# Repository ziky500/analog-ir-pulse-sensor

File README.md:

# Analog IR Pulse Sensor

A simple analog infrared pulse sensor based on reflective photoplethysmography (PPG).

The circuit uses an infrared LED and a photodiode to detect small changes in reflected light caused by blood volume changes in a fingertip. The signal is amplified and filtered using an LM358 operational amplifier.

## My work

The original circuit design was provided by the university as a reference.

I:

- recreated the circuit schematic in KiCad based on the provided design,
- designed the PCB layout in KiCad,
- prepared the single-sided board for CNC milling,
- milled and drilled the PCB at the university,
- manually assembled and soldered the board,
- brought the circuit into operation,
- tested the finished sensor.

## PCB design

The PCB was designed as a single-sided through-hole board suitable for CNC milling.

One crossing connection was implemented as a wire jumper.

A complete PCB layout export is available here:

[PCB layout PDF](exports/pcb_layout.pdf)

## Schematic

The original circuit design was provided by the university. I recreated the schematic in KiCad and used it as the basis for the PCB design.

A PDF version is available here:

[Schematic PDF](exports/schematic.pdf)

## Additional PCB exports

- [Bottom copper layer](exports/pcb_bottom_copper.pdf)
- [Top copper layer](exports/pcb_top_copper.pdf)

## Source files

The editable KiCad project files are available in the [`hardware`](hardware/) directory:

- `senzor_tepu.kicad_pro`
- `senzor_tepu.kicad_sch`
- `senzor_tepu.kicad_pcb`

## Acknowledgements

The original circuit design was provided by the Faculty of Electrical Engineering,
Czech Technical University in Prague (CTU FEL).

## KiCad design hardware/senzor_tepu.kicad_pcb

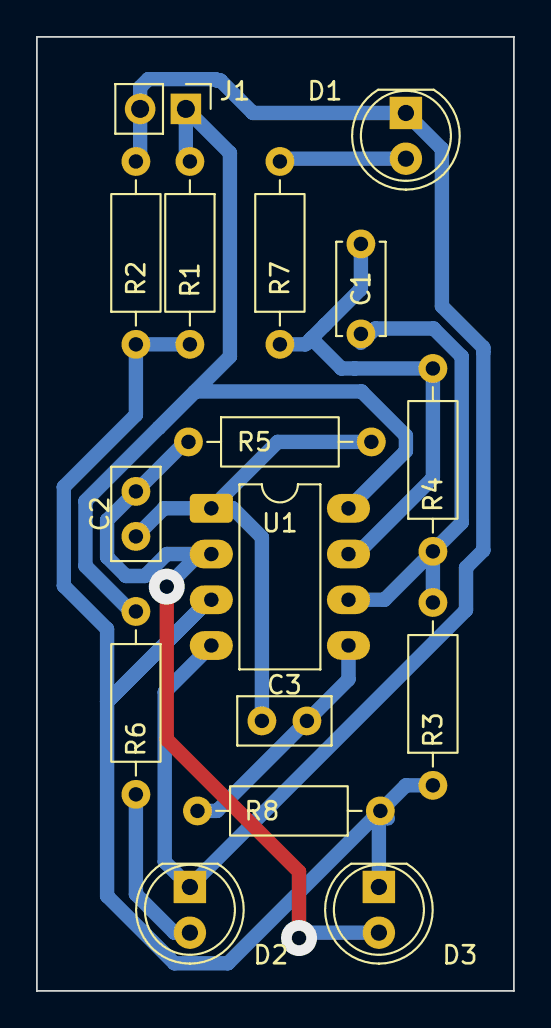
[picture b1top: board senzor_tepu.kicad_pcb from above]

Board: 2 copper layers, 26.5 x 53.0 mm, 16 parts (0 on the bottom side), 10 nets.

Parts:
C1: 100n; C_Disc_D5.0mm_W2.5mm_P5.00mm
C2: 47nF; C_Disc_D5.0mm_W2.5mm_P2.50mm
C3: 1uF; C_Disc_D5.0mm_W2.5mm_P2.50mm
D1: RED; LED_D5.0mm
D2: IR850nm; LED_D5.0mm
D3: D_Photo, 850nm; LED_D5.0mm
J1: Conn_01x02_Pin; PinHeader_1x02_P2.54mm_Vertical
R1, R2, R7: 1k; R_Axial_DIN0207_L6.3mm_D2.5mm_P10.16mm_Horizontal
R3: 4k7; R_Axial_DIN0207_L6.3mm_D2.5mm_P10.16mm_Horizontal
R4: 680k; R_Axial_DIN0207_L6.3mm_D2.5mm_P10.16mm_Horizontal
R5: 1M; R_Axial_DIN0207_L6.3mm_D2.5mm_P10.16mm_Horizontal
R6: 470R; R_Axial_DIN0207_L6.3mm_D2.5mm_P10.16mm_Horizontal
R8: 68k; R_Axial_DIN0207_L6.3mm_D2.5mm_P10.16mm_Horizontal
U1: LM358; DIP-8_W7.62mm_LongPads

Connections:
/+Vcc: J1.1, R1.1, R6.1, U1.8 (V+)
/-Vss: D1.1 (K), D2.1 (K), J1.2, R2.2, U1.4 (V-)
GND: D3.1 (K), R1.2, R2.1, R3.1, R8.1, U1.3 (+)
unnamed: C1.2, R4.2, R7.1, U1.7
unnamed: C2.2, C3.1, R5.2, U1.1
unnamed: D1.2 (A), R7.2
unnamed: D2.2 (A), R6.2
unnamed: C2.1, D3.2 (A), R5.1, U1.2 (-)
unnamed: C3.2, R8.2, U1.5 (+)
unnamed: C1.1, R3.2, R4.1, U1.6 (-)
